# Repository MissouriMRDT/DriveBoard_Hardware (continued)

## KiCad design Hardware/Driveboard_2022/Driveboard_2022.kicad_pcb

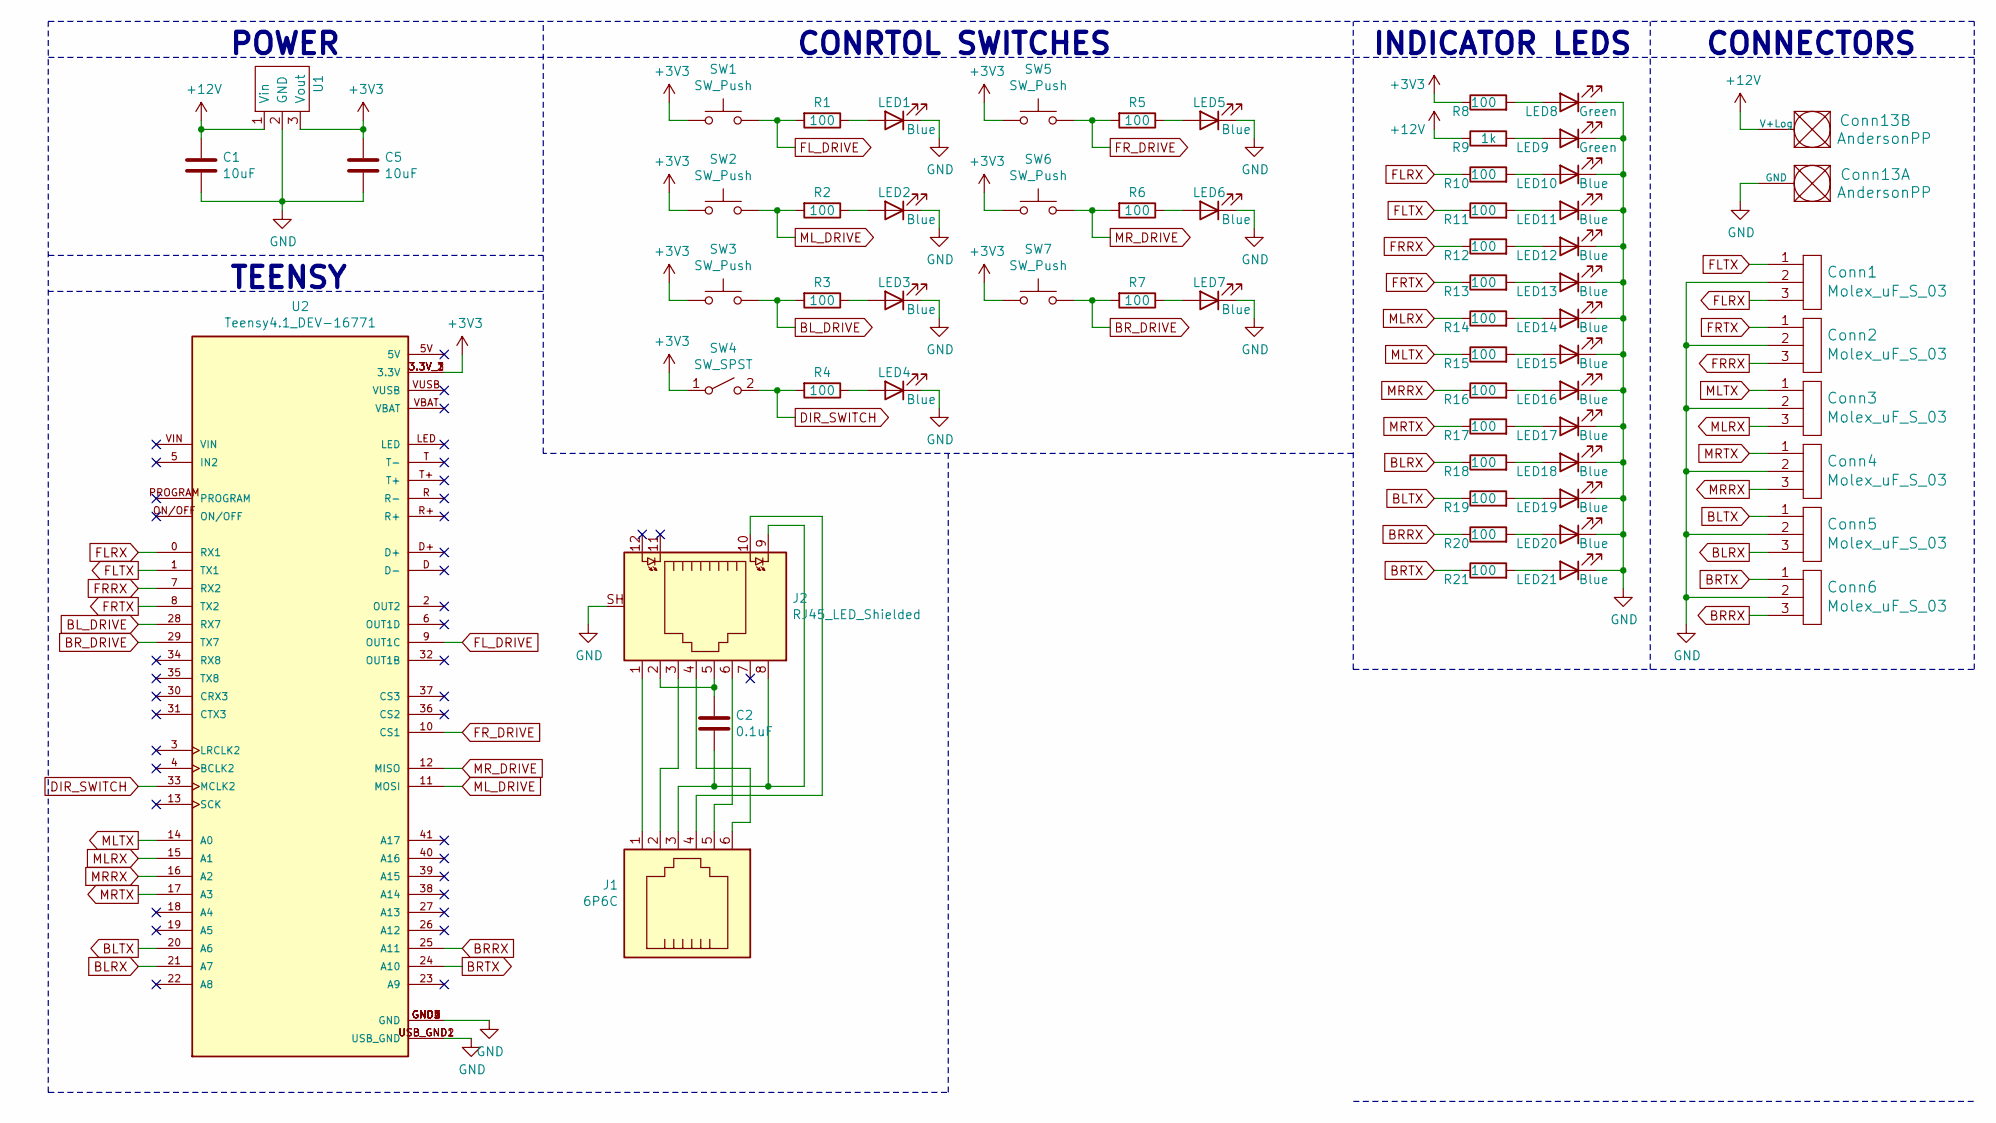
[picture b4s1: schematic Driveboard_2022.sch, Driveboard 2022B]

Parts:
C1, C5: 10uF; C_0603_1608Metric_Pad1.08x0.95mm_HandSolder
C2: 0.1uF; C_0603_1608Metric_Pad1.08x0.95mm_HandSolder
Conn1, Conn2, Conn3, Conn4, Conn5, Conn6: Molex_uF_S_03; MOLEX_uF_S_03_Horizontal
Conn13: AndersonPP; Anderson_2_Horizontal_Side_by_Side
J1: 6P6C; PinHeader_2x03_P2.00mm_Vertical
J2: RJ45_LED_Shielded; RJ45_Teensy
LED1, LED2, LED3, LED4, LED5, LED6, LED7, LED10, LED11, LED12, LED13, LED14, LED15, LED16, LED17, LED18, LED19, LED20, LED21: Blue; LED_0603_1608Metric_Pad1.05x0.95mm_HandSolder
LED8, LED9: Green; LED_0603_1608Metric_Pad1.05x0.95mm_HandSolder
R1, R2, R3, R4, R5, R6, R7, R8, R10, R11, R12, R13, R14, R15, R16, R17, R18, R19, R20, R21: 100; R_0603_1608Metric_Pad0.98x0.95mm_HandSolder
R9: 1k; R_0603_1608Metric_Pad0.98x0.95mm_HandSolder
SW1, SW2, SW3, SW5, SW6, SW7: SW_Push; SW_SPST_TL3305A
SW4: SW_SPST; SW_Slide_1P2T_CK_OS102011MS2Q
U1: TSR1-2433; TSR_1-2433
U2: Teensy4.1_DEV-16771; Teensy_4_1_Vertical; PARTREV 4.1

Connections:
+3V3: C5.1, R8.1, SW1.1, SW2.1, SW3.1, SW4.1 (A), SW5.1, SW6.1, SW7.1, U1.3 (Vout), U2.3.3V_1 (3.3V), U2.3.3V_2 (3.3V), U2.3.3V_3 (3.3V)
+12V: C1.1, Conn13.2 (V+Log), R9.1, U1.1 (Vin)
BLRX: Conn5.3, R18.1, U2.21 (A7)
BLTX: Conn5.1, R19.1, U2.20 (A6)
BL_DRIVE: R3.2, SW3.2, U2.28 (RX7)
BRRX: Conn6.3, R20.1, U2.25 (A11)
BRTX: Conn6.1, R21.1, U2.24 (A10)
BR_DRIVE: R7.2, SW7.2, U2.29 (TX7)
DIR_SWITCH: R4.2, SW4.2 (B), U2.33 (MCLK2)
FLRX: Conn1.3, R10.1, U2.0 (RX1)
FLTX: Conn1.1, R11.1, U2.1 (TX1)
FL_DRIVE: R1.2, SW1.2, U2.9 (OUT1C)
FRRX: Conn2.3, R12.1, U2.7 (RX2)
FRTX: Conn2.1, R13.1, U2.8 (TX2)
FR_DRIVE: R5.2, SW5.2, U2.10 (CS1)
GND: C1.2, C5.2, Conn1.2, Conn2.2, Conn3.2, Conn4.2, Conn5.2, Conn6.2, Conn13.1 (GND), J2.SH, LED1.1 (K), LED2.1 (K), LED3.1 (K), LED4.1 (K), LED5.1 (K), LED6.1 (K), LED7.1 (K), LED8.1 (K), LED9.1 (K), LED10.1 (K), LED11.1 (K), LED12.1 (K), LED13.1 (K), LED14.1 (K), LED15.1 (K), LED16.1 (K), LED17.1 (K), LED18.1 (K), LED19.1 (K), LED20.1 (K), LED21.1 (K), U1.2 (GND), U2.GND1 (GND), U2.GND2 (GND), U2.GND3 (GND), U2.GND4 (GND), U2.GND5 (GND), U2.USB_GND1 (USB_GND), U2.USB_GND2 (USB_GND)
MLRX: Conn3.3, R14.1, U2.15 (A1)
MLTX: Conn3.1, R15.1, U2.14 (A0)
ML_DRIVE: R2.2, SW2.2, U2.11 (MOSI)
MRRX: Conn4.3, R16.1, U2.16 (A2)
MRTX: Conn4.1, R17.1, U2.17 (A3)
MR_DRIVE: R6.2, SW6.2, U2.12 (MISO)
unnamed: C2.1, J2.2, J2.5
unnamed: C2.2, J1.3, J2.8, J2.9
unnamed: J1.1, J2.1
unnamed: J1.2, J2.3
unnamed: J1.4, J2.10
unnamed: J1.5, J2.6
unnamed: J1.6, J2.4
unnamed: LED1.2 (A), R1.1
unnamed: LED2.2 (A), R2.1
unnamed: LED3.2 (A), R3.1
unnamed: LED4.2 (A), R4.1
unnamed: LED5.2 (A), R5.1
unnamed: LED6.2 (A), R6.1
unnamed: LED7.2 (A), R7.1
unnamed: LED8.2 (A), R8.2
unnamed: LED9.2 (A), R9.2
unnamed: LED10.2 (A), R10.2
unnamed: LED11.2 (A), R11.2
unnamed: LED12.2 (A), R12.2
unnamed: LED13.2 (A), R13.2
unnamed: LED14.2 (A), R14.2
unnamed: LED15.2 (A), R15.2
unnamed: LED16.2 (A), R16.2
unnamed: LED17.2 (A), R17.2
unnamed: LED18.2 (A), R18.2
unnamed: LED19.2 (A), R19.2
unnamed: LED20.2 (A), R20.2
unnamed: LED21.2 (A), R21.2

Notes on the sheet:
POWER
INDICATOR LEDS
CONNECTORS
CONRTOL SWITCHES
TEENSY

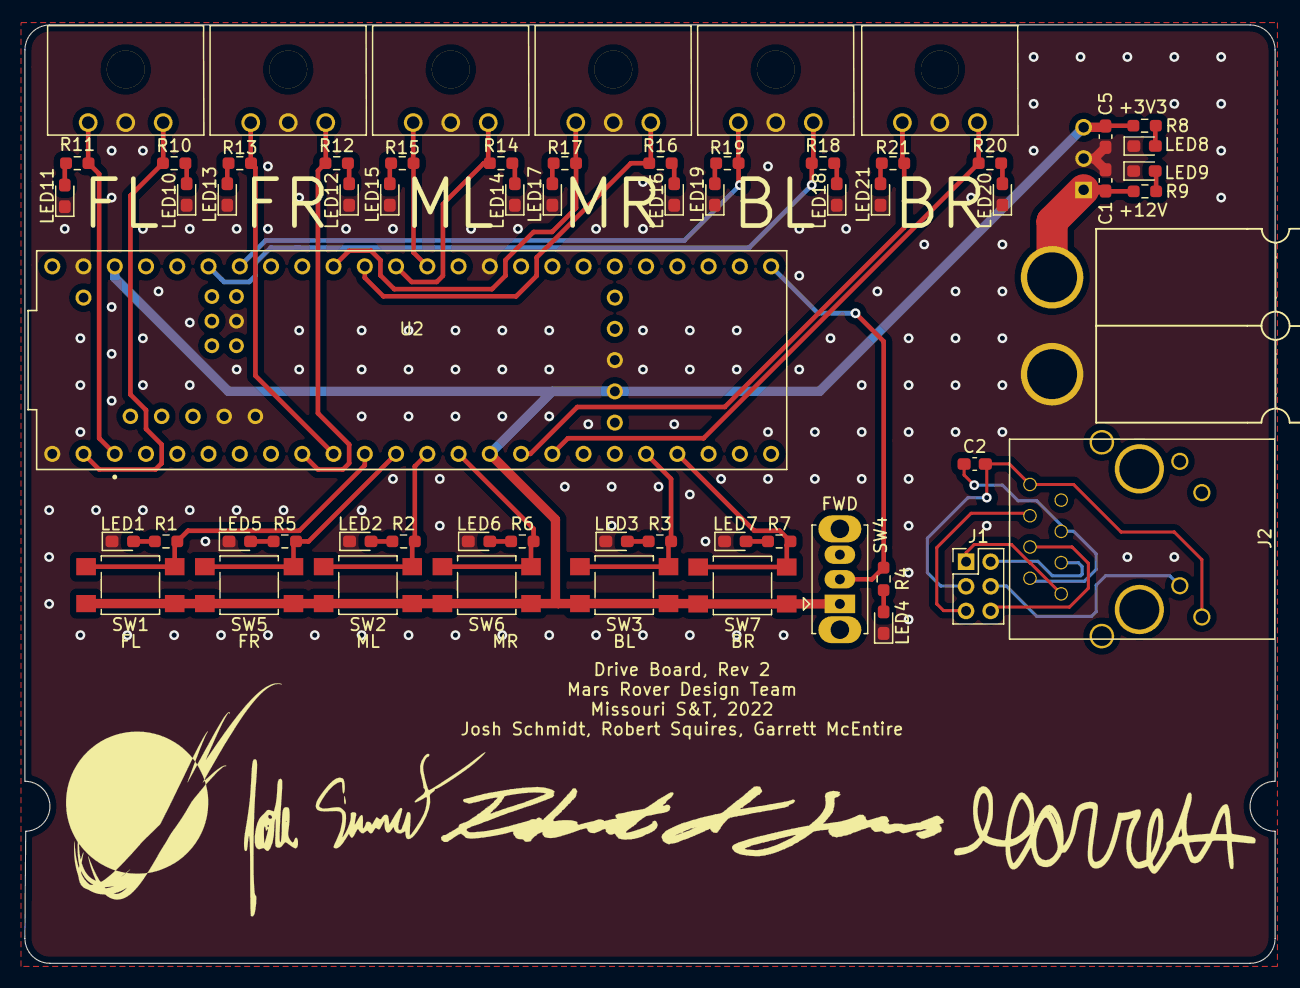
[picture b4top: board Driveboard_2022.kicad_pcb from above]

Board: 2 copper layers, 101.6 x 76.3 mm, 63 parts (1 on the bottom side), 50 nets.

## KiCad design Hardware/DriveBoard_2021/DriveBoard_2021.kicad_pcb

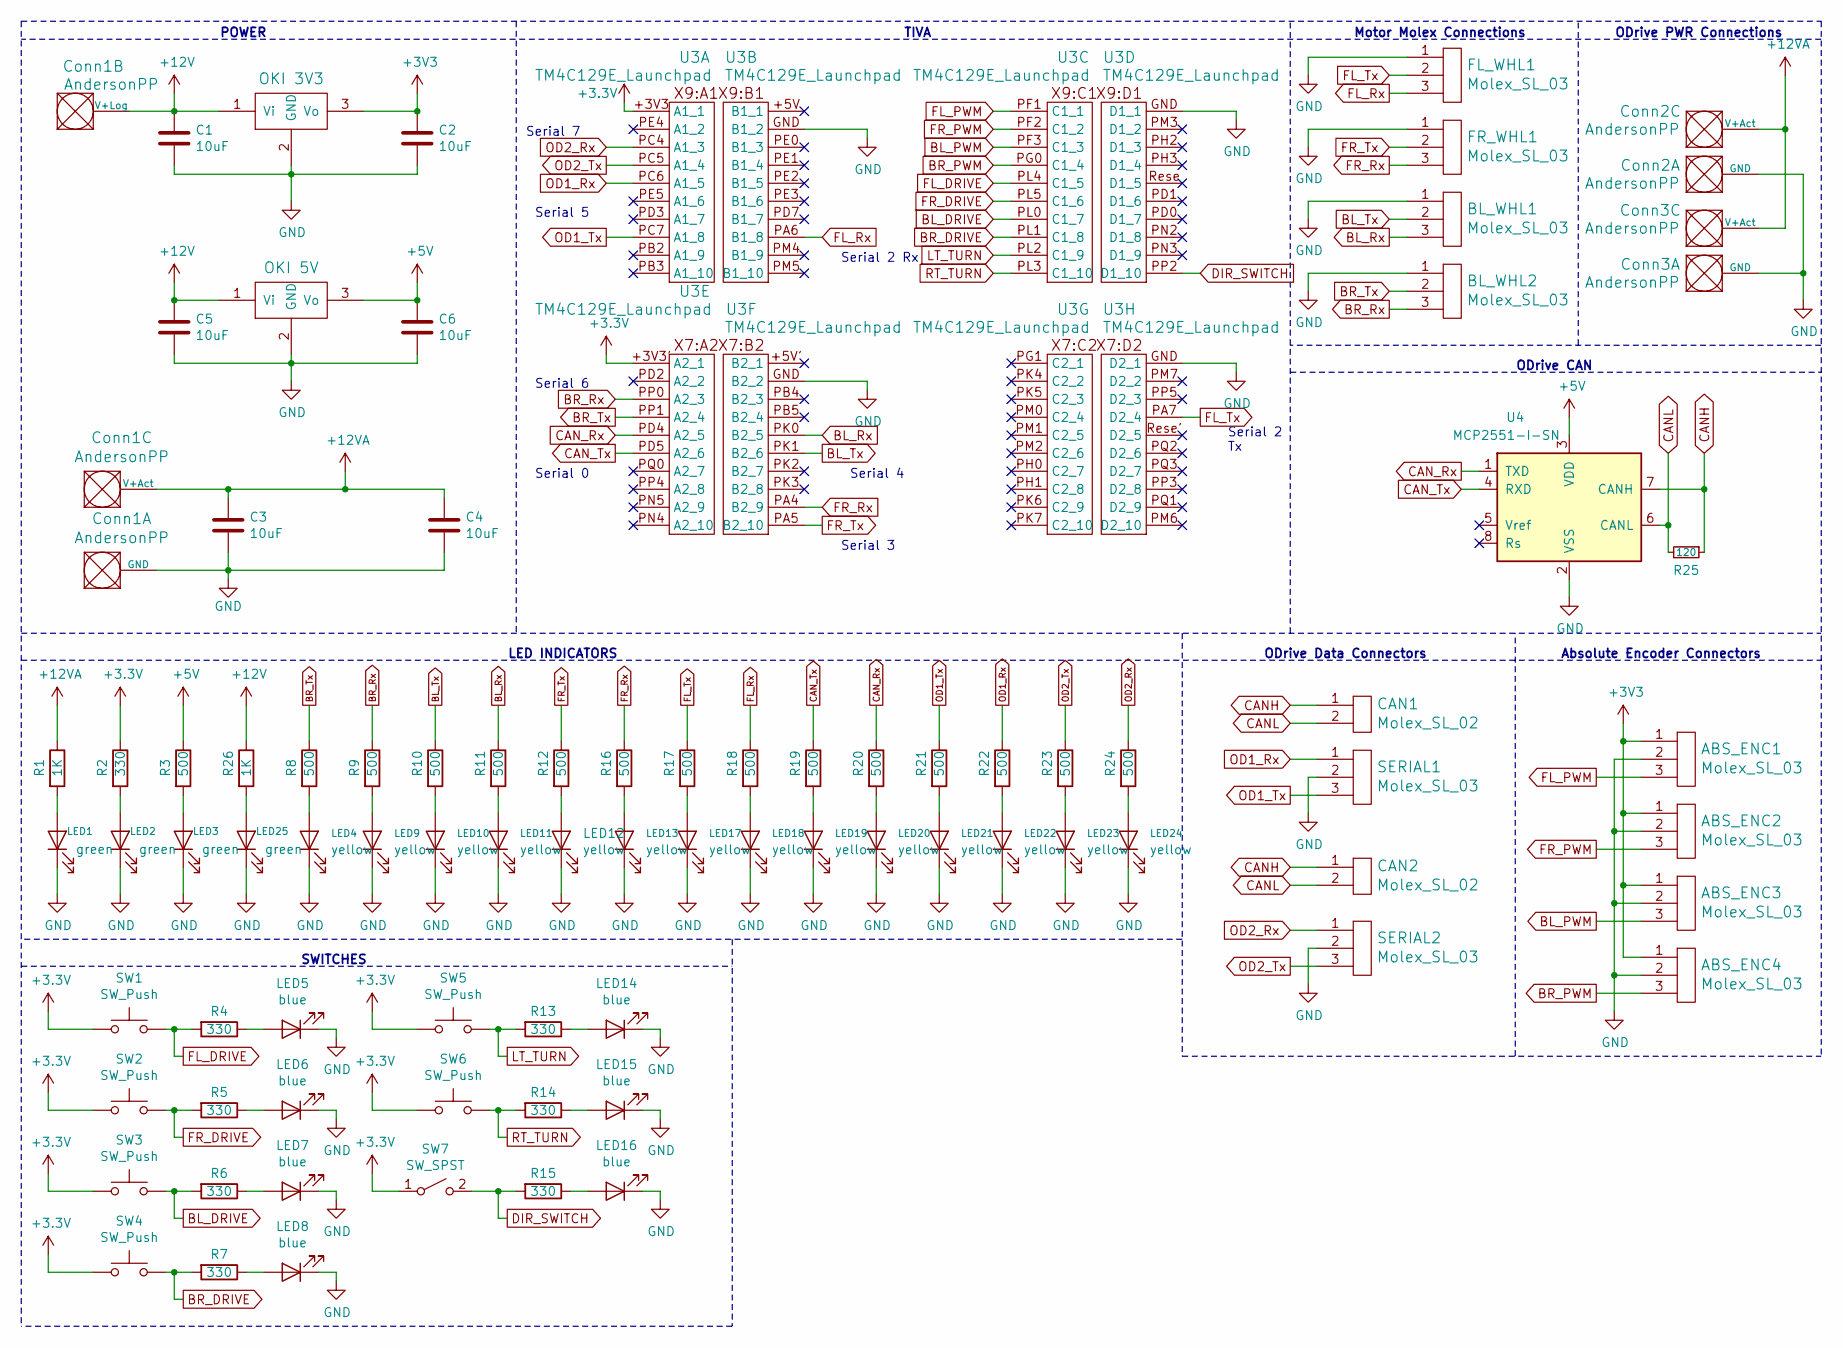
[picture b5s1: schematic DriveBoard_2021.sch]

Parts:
ABS_ENC1, ABS_ENC2, ABS_ENC3, ABS_ENC4: Molex_SL_03; MOLEX_SL_03_Horizontal
BL_WHL1, BL_WHL2: Molex_SL_03; MOLEX_SL_03_Horizontal
C1, C2, C3, C4, C5, C6: 10uF; C_0603_1608Metric_Pad1.05x0.95mm_HandSolder
CAN1, CAN2: Molex_SL_02; MOLEX_SL_02_Horizontal
Conn1: AndersonPP; Anderson_3_Horizontal_Side_by_Side
Conn2, Conn3: AndersonPP; Anderson_2_Horizontal_Side_by_Side
FL_WHL1: Molex_SL_03; MOLEX_SL_03_Horizontal
FR_WHL1: Molex_SL_03; MOLEX_SL_03_Horizontal
LED1, LED2, LED3, LED25: green; LED_0603_1608Metric_Pad1.05x0.95mm_HandSolder
LED4, LED9, LED10, LED11, LED12, LED13, LED17, LED18, LED19, LED20, LED21, LED22, LED23, LED24: yellow; LED_0603_1608Metric_Pad1.05x0.95mm_HandSolder
LED5, LED6, LED7, LED8, LED14, LED15, LED16: blue; LED_0603_1608Metric_Pad1.05x0.95mm_HandSolder
R1, R26: 1K; R_0603_1608Metric_Pad1.05x0.95mm_HandSolder
R2, R4, R5, R6, R7, R13, R14, R15: 330; R_0603_1608Metric_Pad1.05x0.95mm_HandSolder
R3, R8, R9, R10, R11, R12, R16, R17, R18, R19, R20, R21, R22, R23, R24: 500; R_0603_1608Metric_Pad1.05x0.95mm_HandSolder
R25: 120; R_0603_1608Metric_Pad1.05x0.95mm_HandSolder
SERIAL1, SERIAL2: Molex_SL_03; MOLEX_SL_03_Horizontal
SW1, SW2, SW3, SW4, SW5, SW6: SW_Push; SW_SPST_TL3305A
SW7: SW_SPST; SW_CuK_JS202011CQN_DPDT_Straight
U1: OKI 3V3; OKI_Horizontal
U2: OKI 5V; OKI_Horizontal
U3: TM4C129E_Launchpad; TM4C129E_Launchpad_FULL_THT_BOTTOM
U4: MCP2551-I-SN; SOIC-8_3.9x4.9mm_P1.27mm

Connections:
+5V: C6.1, R3.1, U2.3 (Vo), U4.3 (VDD)
+12V: C1.1, C5.1, Conn1.2 (V+Log), R26.1, U1.1 (Vi), U2.1 (Vi)
+12VA: C3.1, C4.1, Conn1.3 (V+Act), Conn2.2 (V+Log), Conn3.2 (V+Log), R1.1
BL_DRIVE: R6.2, SW3.2, U3.PL0 (C1_7)
BL_PWM: ABS_ENC3.3, U3.PF3 (C1_3)
BL_Rx: BL_WHL1.3, R11.1, U3.PK0 (B2_5)
BL_Tx: BL_WHL1.2, R10.1, U3.PK1 (B2_6)
BR_DRIVE: R7.2, SW4.2, U3.PL1 (C1_8)
BR_PWM: ABS_ENC4.3, U3.PG0 (C1_4)
BR_Rx: BL_WHL2.3, R9.1, U3.PP0 (A2_3)
BR_Tx: BL_WHL2.2, R8.1, U3.PP1 (A2_4)
CANH: CAN1.1, CAN2.1, R25.1, U4.7 (CANH)
CANL: CAN1.2, CAN2.2, R25.2, U4.6 (CANL)
CAN_Rx: R20.1, U3.PD4 (A2_5), U4.1 (TXD)
CAN_Tx: R19.1, U3.PD5 (A2_6), U4.4 (RXD)
DIR_SWITCH: R15.2, SW7.2 (B), U3.PP2 (D1_10)
FL_DRIVE: R4.2, SW1.2, U3.PL4 (C1_5)
FL_PWM: ABS_ENC1.3, U3.PF1 (C1_1)
FL_Rx: FL_WHL1.3, R18.1, U3.PA6 (B1_8)
FL_Tx: FL_WHL1.2, R17.1, U3.PA7 (D2_4)
FR_DRIVE: R5.2, SW2.2, U3.PL5 (C1_6)
FR_PWM: ABS_ENC2.3, U3.PF2 (C1_2)
FR_Rx: FR_WHL1.3, R16.1, U3.PA4 (B2_9)
FR_Tx: FR_WHL1.2, R12.1, U3.PA5 (B2_10)
GND: ABS_ENC1.2, ABS_ENC2.2, ABS_ENC3.2, ABS_ENC4.2, BL_WHL1.1, BL_WHL2.1, C1.2, C2.2, C3.2, C4.2, C5.2, C6.2, Conn1.1 (GND), Conn2.1 (GND), Conn3.1 (GND), FL_WHL1.1, FR_WHL1.1, LED1.1 (K), LED2.1 (K), LED3.1 (K), LED4.1 (K), LED5.1 (K), LED6.1 (K), LED7.1 (K), LED8.1 (K), LED9.1 (K), LED10.1 (K), LED11.1 (K), LED12.1 (K), LED13.1 (K), LED14.1 (K), LED15.1 (K), LED16.1 (K), LED17.1 (K), LED18.1 (K), LED19.1 (K), LED20.1 (K), LED21.1 (K), LED22.1 (K), LED23.1 (K), LED24.1 (K), LED25.1 (K), SERIAL1.2, SERIAL2.2, U1.2 (GND), U2.2 (GND), U3.GND (B1_2), U4.2 (VSS)
LT_TURN: R13.2, SW5.2, U3.PL2 (C1_9)
unnamed: LED1.2 (A), R1.2
unnamed: LED2.2 (A), R2.2
unnamed: LED3.2 (A), R3.2
unnamed: LED4.2 (A), R8.2
unnamed: LED5.2 (A), R4.1
unnamed: LED6.2 (A), R5.1
unnamed: LED7.2 (A), R6.1
unnamed: LED8.2 (A), R7.1
unnamed: LED9.2 (A), R9.2
unnamed: LED10.2 (A), R10.2
unnamed: LED11.2 (A), R11.2
unnamed: LED12.2 (A), R12.2
unnamed: LED13.2 (A), R16.2
unnamed: LED14.2 (A), R13.1
unnamed: LED15.2 (A), R14.1
unnamed: LED16.2 (A), R15.1
unnamed: LED17.2 (A), R17.2
unnamed: LED18.2 (A), R18.2
unnamed: LED19.2 (A), R19.2
unnamed: LED20.2 (A), R20.2
unnamed: LED21.2 (A), R21.2
unnamed: LED22.2 (A), R22.2
unnamed: LED23.2 (A), R23.2
unnamed: LED24.2 (A), R24.2
unnamed: LED25.2 (A), R26.2
OD1_Rx: R22.1, SERIAL1.1, U3.PC6 (A1_5)
OD1_Tx: R21.1, SERIAL1.3, U3.PC7 (A1_8)
OD2_Rx: R24.1, SERIAL2.1, U3.PC4 (A1_3)
OD2_Tx: R23.1, SERIAL2.3, U3.PC5 (A1_4)
RT_TURN: R14.2, SW6.2, U3.PL3 (C1_10)

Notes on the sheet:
POWER
SWITCHES
LED INDICATORS
TIVA
Serial 4
Serial 3
Serial 6
Serial 2 Rx
Serial 2 Tx
Motor Molex Connections
ODrive PWR Connections
Serial 0
ODrive CAN
Serial 5
Serial 7
Absolute Encoder Connectors
ODrive Data Connectors

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
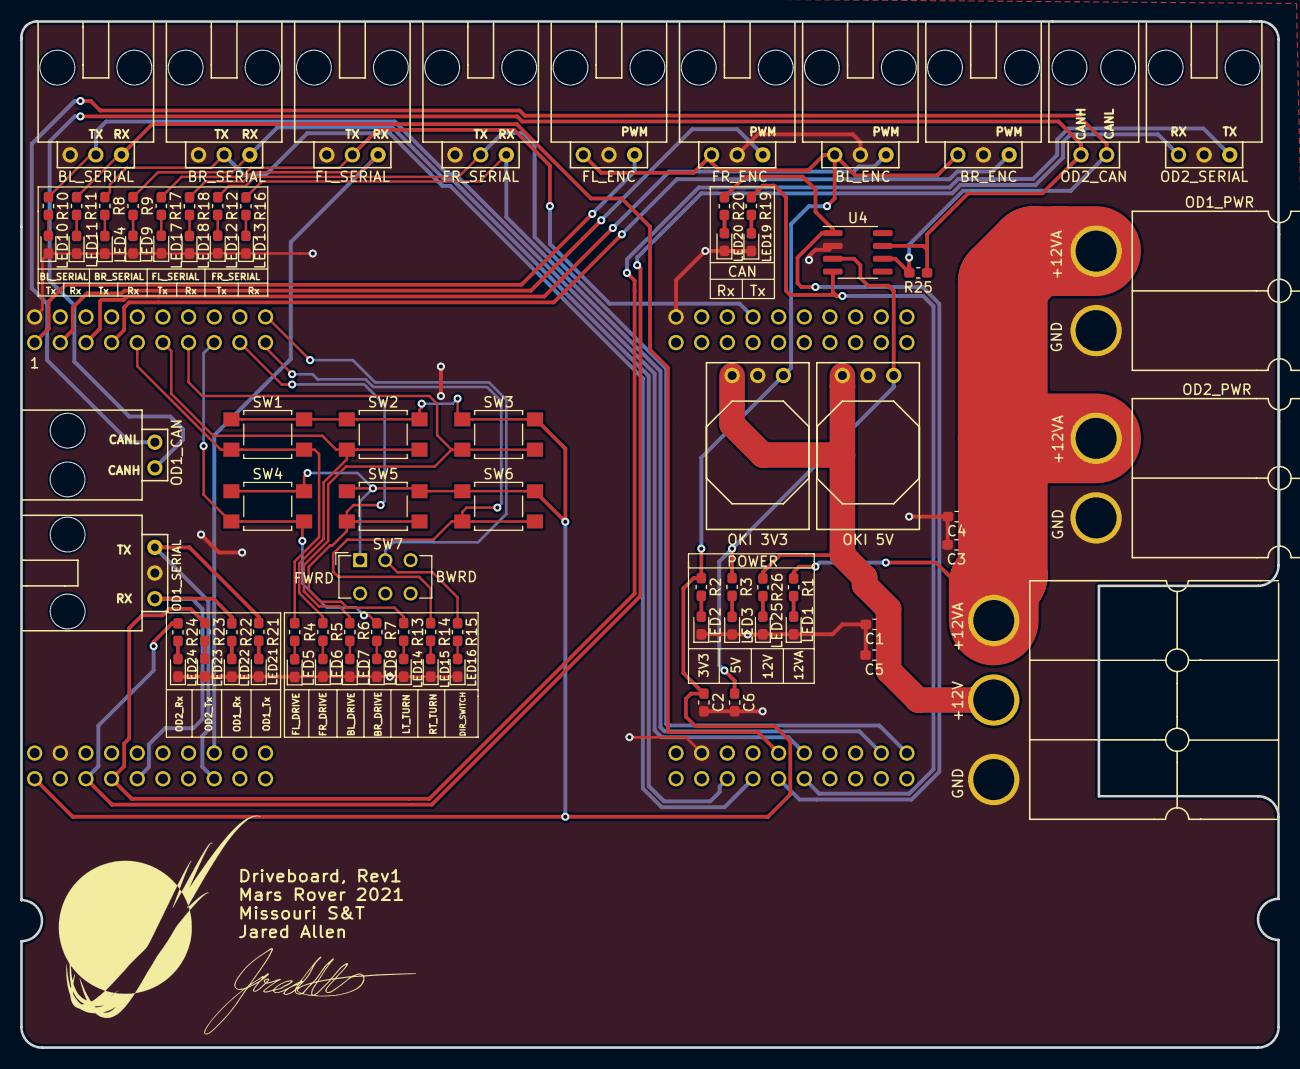
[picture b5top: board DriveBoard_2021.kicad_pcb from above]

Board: 2 copper layers, 124.5 x 101.6 mm, 83 parts (0 on the bottom side), 57 nets.

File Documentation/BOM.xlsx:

Id | Designator | Package | Quantity | Designation | Supplier and ref
1 | R11,R3,R8,R9,R10,R12,R16,R17,R18,R19,R20,R21,R22,R23,R24 | R_0603_1608Metric_Pad1.05x0.95mm_HandSolder | 15 | 500
2 | U3 | TM4C129E_Launchpad_FULL_THT_BOTTOM | 1 | TM4C129E_Launchpad
3 | G*** | 0_MRDT_Logo_20mm | 1 | LOGO
4 | G*** | z_sig_Jared_Allen | 1 | LOGO
5 | Conn1 | Anderson_3_Horizontal_Side_by_Side | 1 | AndersonPP
6 | FR_WHL1,FL_WHL1,BL_WHL2,BL_WHL1,ABS_ENC4,ABS_ENC3,ABS_ENC2,ABS_ENC1,SERIAL1,SER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 | MOLEX_SL_03_Horizontal | 10 | Molex_SL_03
7 | Conn3,Conn2 | Anderson_2_Horizontal_Side_by_Side | 2 | AndersonPP
8 | CAN2,CAN1 | MOLEX_SL_02_Horizontal | 2 | Molex_SL_02
9 | C1,C2,C3,C4,C5,C6 | C_0603_1608Metric_Pad1.05x0.95mm_HandSolder | 6 | 10uF
10 | LED1,LED2,LED3,LED25 | LED_0603_1608Metric_Pad1.05x0.95mm_HandSolder | 4 | green
11 | LED4,LED9,LED10,LED11,LED12,LED13,LED17,LED18,LED19,LED20,LED21,LED22,LED23,LED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 | LED_0603_1608Metric_Pad1.05x0.95mm_HandSolder | 14 | pink
12 | LED5,LED6,LED7,LED8,LED14,LED15,LED16 | LED_0603_1608Metric_Pad1.05x0.95mm_HandSolder | 7 | yellow
13 | R1,R26 | R_0603_1608Metric_Pad1.05x0.95mm_HandSolder | 2 | 1K
14 | R2,R4,R5,R6,R7,R13,R14,R15 | R_0603_1608Metric_Pad1.05x0.95mm_HandSolder | 8 | 330
15 | R25 | R_0603_1608Metric_Pad1.05x0.95mm_HandSolder | 1 | 120
16 | FL_DRIVE,FR_DRIVE,BL_DRIVE,BR_DRIVE,LT_TURN,RT_TURN | SW_SPST_TL3305A | 6 | SW_Push
17 | DIR_SWITCH | SW_CuK_JS202011CQN_DPDT_Straight | 1 | SW_SPST
18 | U1 | OKI_Horizontal | 1 | OKI 3V3
19 | U2 | OKI_Horizontal | 1 | OKI 5V
20 | CAN | SOIC-8_3.9x4.9mm_P1.27mm | 1 | MCP2551-I-SN

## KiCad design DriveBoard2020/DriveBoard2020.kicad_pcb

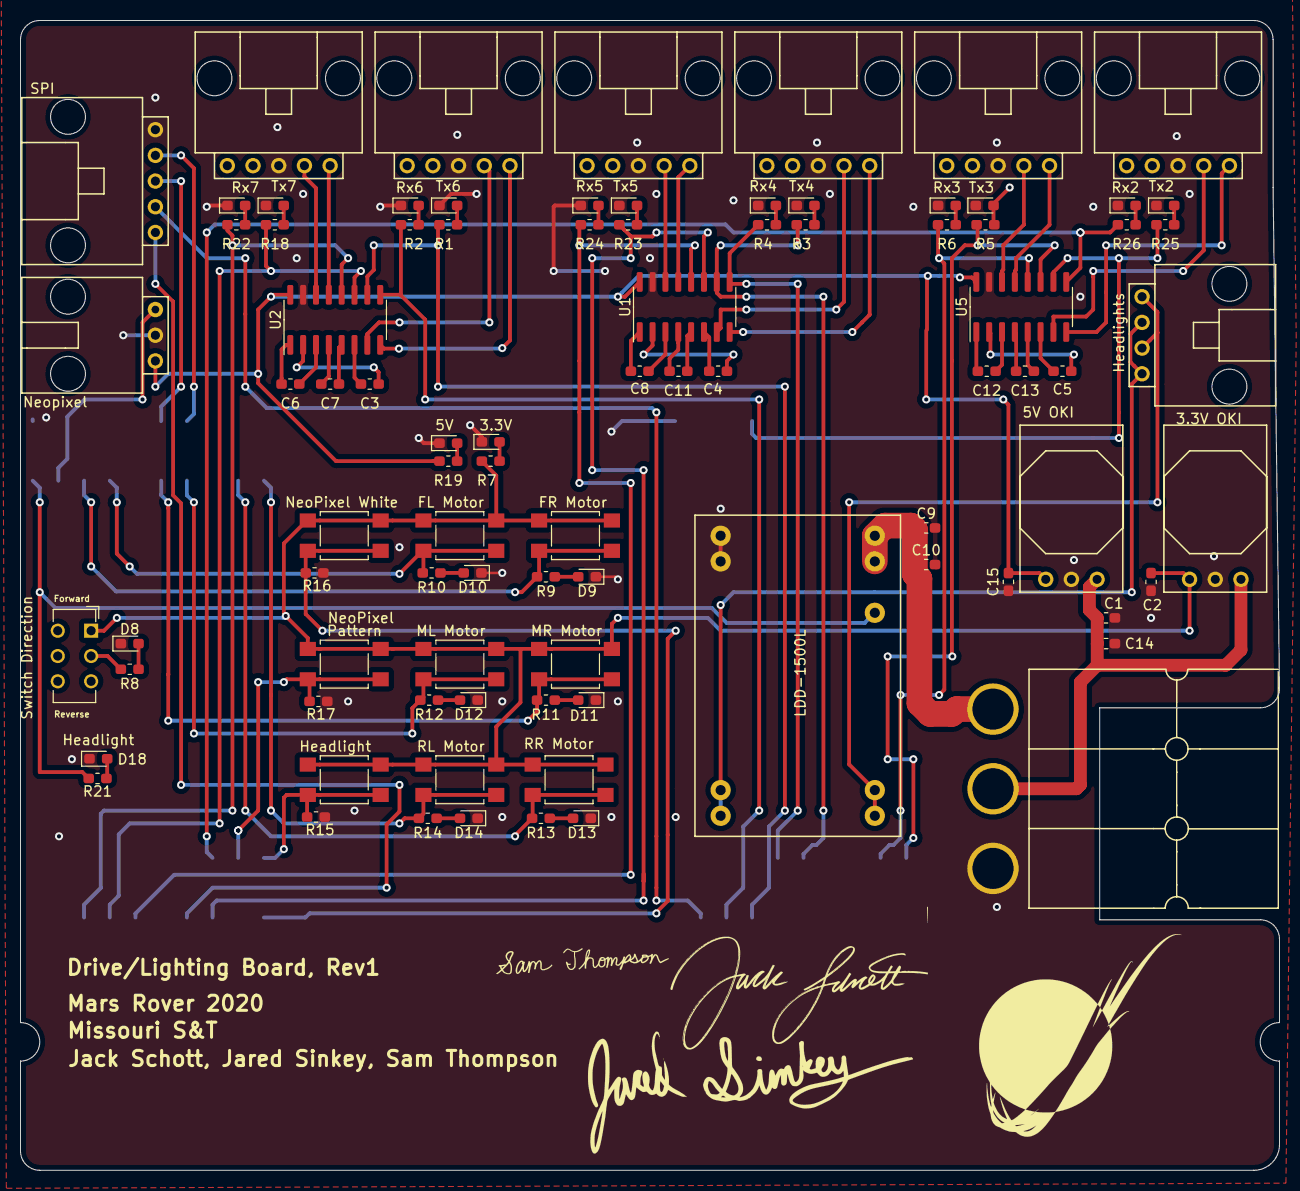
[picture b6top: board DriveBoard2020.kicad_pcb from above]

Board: 2 copper layers, 124.5 x 113.7 mm, 89 parts (0 on the bottom side), 87 nets.

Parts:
3.3V, 5V: LED; LED_0603_1608Metric_Pad1.05x0.95mm_HandSolder
C1, C2, C9, C10, C14, C15: 10uF; C_0603_1608Metric_Pad1.05x0.95mm_HandSolder
C3, C4, C5: 1uF; C_0603_1608Metric_Pad1.05x0.95mm_HandSolder
C6, C7, C8, C11, C12, C13: .1uF; C_0603_1608Metric_Pad1.05x0.95mm_HandSolder
Conn1: AndersonPP; Anderson_3_Horizontal_Side_by_Side
Conn2, Conn3, Conn4, Conn5, Conn6, Conn7, Conn12: Molex_SL_05; MOLEX_SL_05_Horizontal
Conn9: Molex_SL_03; MOLEX_SL_03_Horizontal
Conn10: Molex_SL_04; MOLEX_SL_04_Horizontal
D8, D9, D10, D11, D12, D13, D14: LED; LED_0603_1608Metric_Pad1.05x0.95mm_HandSolder
FL Motor: SW_Push; SW_SPST_TL3305A
FR Motor: SW_Push; SW_SPST_TL3305A
Headlight: SW_Push; SW_SPST_TL3305A
Headlight#2: LED; LED_0603_1608Metric_Pad1.05x0.95mm_HandSolder
ML Motor: SW_Push; SW_SPST_TL3305A
MR Motor: SW_Push; SW_SPST_TL3305A
NeoPixel White: SW_Push; SW_SPST_TL3305A
Pattern: SW_Push; SW_SPST_TL3305A
R1, R2, R3, R4, R5, R6, R18, R19, R21, R22, R23, R24, R25, R26: 500; R_0603_1608Metric_Pad1.05x0.95mm_HandSolder
R7, R8, R9, R10, R11, R12, R13, R14: 330; R_0603_1608Metric_Pad1.05x0.95mm_HandSolder
R15, R16, R17: 10k; R_0603_1608Metric_Pad1.05x0.95mm_HandSolder
RL Motor: SW_Push; SW_SPST_TL3305A
RR Motor: SW_Push; SW_SPST_TL3305A
Rx2, Rx3, Rx4, Rx5, Rx6, Rx7: LED; LED_0603_1608Metric_Pad1.05x0.95mm_HandSolder
Switch Direction: SW_SPST; SW_CuK_JS202011CQN_DPDT_Straight
Tx2, Tx3, Tx4, Tx5, Tx6, Tx7: LED; LED_0603_1608Metric_Pad1.05x0.95mm_HandSolder
U1, U2, U5: MAX_3232; SOIC-16_3.9x9.9mm_P1.27mm
U3: 3.3V OKI; OKI_Horizontal
U4: TM4C129E_Launchpad; TM4C129E_Launchpad_FULL_SMD_BOTTOM
U6: 5V OKI; OKI_Horizontal
U8: LDD-1500L; LDD-1500L_LED_DRIVER

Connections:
+3V3: C2.1, FL Motor.1, FR Motor.1, Headlight.1, ML Motor.1, MR Motor.1, NeoPixel White.1, Pattern.1, R7.1, RL Motor.1, RR Motor.1, Switch Direction.1, U3.3
+5V: C15.1, Conn9.1, R19.1, U1.16, U2.16, U5.16, U6.3
+12V: C1.1, C14.1, Conn1.2, U3.1, U6.1
+12VA: C9.1, C10.1, Conn1.3, U8.23, U8.24
CLK2: Conn12.1, U4.PD3
CS2: Conn12.2, U4.PD2
Dout_NeoPixel: Conn9.3, U4.PF2
FL_In: Conn2.5, U2.13
FL_Motor: FL Motor.2, R10.2, U4.PG0
FL_Out: Conn2.4, U2.14
FR_In: Conn5.5, U2.8
FR_Motor: FR Motor.2, R9.2, U4.PF3
FR_Out: Conn5.4, U2.7
GND: 3.3V.1, 5V.1, C1.2, C2.2, C9.2, C10.2, C14.2, C15.2, Conn1.1, Conn2.3, Conn3.3, Conn4.3, Conn5.3, Conn6.3, Conn7.3, Conn9.2, Conn12.5, D8.1, D9.1, D10.1, D11.1, D12.1, D13.1, D14.1, Headlight#2.1, R15.1, R16.1, R17.1, Rx2.1, Rx3.1, Rx4.1, Rx5.1, Rx6.1, Rx7.1, Tx2.1, Tx3.1, Tx4.1, Tx5.1, Tx6.1, Tx7.1, U1.15, U2.15, U3.2, U4.GND, U5.15, U6.2, U8.1, U8.2
Headlight_OnOff_PWM: R21.1, U4.PF1, U8.21
Headlight_Power: Headlight.2, R15.2, U4.PM5
MISO2: Conn12.4, U4.PD0
ML_In: Conn3.5, U1.13
ML_Motor: ML Motor.2, R12.2, U4.PL0
ML_Out: Conn3.4, U1.14
MOSI2: Conn12.3, U4.PD1
MR_In: Conn6.5, U1.8
MR_Motor: MR Motor.2, R11.2, U4.PL5
MR_Out: Conn6.4, U1.7
NeoPixel_Pattern: Pattern.2, R17.2, U4.PM4
NeoPixel_White: NeoPixel White.2, R16.2, U4.PB3
unnamed: C3.1, U2.2
unnamed: C3.2, U2.6
unnamed: C4.1, U1.2
unnamed: C4.2, U1.6
unnamed: C5.1, U5.2
unnamed: C5.2, U5.6
unnamed: C6.1, U2.1
unnamed: C6.2, U2.3
unnamed: C7.1, U2.4
unnamed: C7.2, U2.5
unnamed: C8.1, U1.1
unnamed: C8.2, U1.3
unnamed: C11.1, U1.4
unnamed: C11.2, U1.5
unnamed: C12.1, U5.1
unnamed: C12.2, U5.3
unnamed: C13.1, U5.4
unnamed: C13.2, U5.5
unnamed: Conn10.1, Conn10.3, U8.13, U8.14
unnamed: Conn10.2, Conn10.4, U8.11, U8.12
unnamed: R1.2, Tx6.2
unnamed: R2.2, Rx6.2
unnamed: R3.2, Tx4.2
unnamed: R4.2, Rx4.2
unnamed: R5.2, Tx3.2
unnamed: R6.2, Rx3.2
unnamed: 3.3V.2, R7.2
unnamed: D8.2, R8.1
unnamed: D9.2, R9.1
unnamed: D10.2, R10.1
unnamed: D11.2, R11.1
unnamed: D12.2, R12.1
unnamed: D13.2, R13.1
unnamed: D14.2, R14.1
unnamed: R18.2, Tx7.2
unnamed: 5V.2, R19.2
unnamed: Headlight#2.2, R21.2
unnamed: R22.2, Rx7.2
unnamed: R23.2, Tx5.2
unnamed: R24.2, Rx5.2
unnamed: R25.2, Tx2.2
unnamed: R26.2, Rx2.2
RL_In: Conn4.5, U5.13
RL_Motor: R14.2, RL Motor.2, U4.PL3
RL_Out: Conn4.4, U5.14
RR_In: Conn7.5, U5.8
RR_Motor: R13.2, RR Motor.2, U4.PL2
RR_Out: Conn7.4, U5.7
Rx2: R26.1, U4.PA6, U5.9
Rx3: R6.1, U4.PA4, U5.12
Rx4: R4.1, U1.9, U4.PK0
Rx5: R24.1, U1.12, U4.PC6
Rx6: R2.1, U2.9, U4.PP0
Rx7: R22.1, U2.12, U4.PC4
Tx2: R25.1, U4.PA7, U5.10
Tx3: R5.1, U4.PA5, U5.11
Tx4: R3.1, U1.10, U4.PK1
Tx5: R23.1, U1.11, U4.PC7
Tx6: R1.1, U2.10, U4.PP1
Tx7: R18.1, U2.11, U4.PC5
switch_direction: R8.2, Switch Direction.2

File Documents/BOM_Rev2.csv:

Id,Designator,Package,,Designation,Item Name,Part Number,,Vendor,Quantity,Cost Per Item,,Cost,URL,Comments
1,U4,TM4C129E_Launchpad_FULL_THT_BOTTOM,,TM4C129E_Launchpad,LAUNCHPAD TM4C129E EVAL BRD,296-44249-ND,,digikey,1,25.95,,25.95,https://www.digikey.com/products/en?keywords=tm4c129e%20launchpad,
2,"C1,C2,C9,C10,C14,C15",C_0603_1608Metric_Pad1.05x0.95mm_HandSolder,,10uF,CAP CER 10UF 6.3V X5R 0603,1276-3105-6-ND,,digikey,6,0.29,,1.74,https://www.digikey.com/product-detail/en/samsung-electro-me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,
3,"C3,C4,C5",C_0603_1608Metric_Pad1.05x0.95mm_HandSolder,,1uF,CAP CER 1UF 616V X7R 0603,1276-6524-1-ND,,digikey,6,0.1,,0.6,https://www.digikey.com/products/en?keywords=1276-6524-1-ND,
4,"C6,C7,C8,C11,C12,C13",C_0603_1608Metric_Pad1.05x0.95mm_HandSolder,,.1uF,CAP CER 0.1UF 16V X7R 0603,1276-1005-1-ND,,digikey,6,0.1,,0.6,https://www.digikey.com/products/en?keywords=1276-1005-1-ND,
5,"D8,D9,D10,D11,D12,D13,D14",LED_0603_1608Metric_Pad1.05x0.95mm_HandSolder,,Orange 0603,LED ORANGE CLEAR SMD,160-1445-1-ND,,digikey,7,0.26,,1.82,https://www.digikey.com/product-detail/en/lite-on-inc/LTST-C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,
6,"Tx2,Rx2,Tx3,Rx3,Tx4,Rx4,Tx5,Rx5,Tx6,Rx6,Tx7,Rx7,",LED_0603_1608Metric_Pad1.05x0.95mm_HandSolder,,Pink 0603,SMD LED - 0603 PINK,n/a,,aliexpress,12,0.64,,7.68,https://www.aliexpress.com/item/32723711697.html?scm=1007.23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,
7,3.3V,LED_0603_1608Metric_Pad1.05x0.95mm_HandSolder,,Green 0603,LED GREEN CLEAR SMD,160-1446-1-ND,,digikey,1,0.28,,0.28,https://www.digikey.com/product-detail/en/lite-on-inc/LTST-C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,
8,5V,LED_0603_1608Metric_Pad1.05x0.95mm_HandSolder,,Yellow 0603,LED YELLOW CLEAR SMD,160-1448-1-ND,,digikey,1,0.28,,0.28,https://www.digikey.com/product-detail/en/lite-on-inc/LTST-C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,
9,"R1,R2,R3,R4,R5,R6,R16,R17,R19,R18,R22,R23,R24,R25,R26",R_0603_1608Metric_Pad1.05x0.95mm_HandSolder,,500,RES SMD 510 OHM 5% 1/4W 0603,RHM510DCT-ND,,digikey,15,0.1,,1.5,https://www.digikey.com/products/en?keywords=RHM510DCT-ND,
10,"R7,R8,R9,R11,R13,R15,R10,R12,R14",R_0603_1608Metric_Pad1.05x0.95mm_HandSolder,,330,RES SMD 330 OHM 5% 1/4W 0603,RHM330DCT-ND,,digikey,9,0.1,,0.9,https://www.digikey.com/product-detail/en/rohm-semiconductor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,
11,"U3,U6",OKI_Horizontal,,OKI,DC DC CONVERTER 3.3V 5W,811-3014-ND,,digikey,2,4.3,,8.6,https://www.digikey.com/products/en?keywords=811-3014-ND,
12,Change Direction,SW_CuK_OS102011MA1QN1_SPDT_Angled,,SW_SPST,SWITCH SLIDE SPDT 100MA 12V,CKN9559-ND,,digikey,1,0.38,,0.38,https://www.digikey.com/products/en?keywords=CKN9559-ND,
13,"Middle Right,Rear Right,Headlights,Neopixel White,Neopixel,Front Left,Middle Left,Rear Left,Front Right",SW_SPST_TL3305A,,SW_Push,SWITCH TACTILE SPST-NO 50MA 12V,EG5350CT-ND,,digikey,9,0.2,,1.8,https://www.digikey.com/products/en?keywords=EG5350CT-ND,
14,"Conn2,Conn3,Conn4,Conn5,Conn6,Conn7,Conn12",MOLEX_SL_05_Vertical,,Molex_SL_05,CONN HEADER R/A 5POS 2.54MM,WM4903-ND,,digikey,7,1.23,,8.61,https://www.digikey.com/products/en?keywords=WM4903-ND,
15,"U1,U2,U5",SOIC-16_3.9x9.9mm_P1.27mm,,MAX_3232,IC TRANSCEIVER FULL 2/2 16SOIC,296-13094-1-ND,,digikey,3,1.89,,5.67,https://www.digikey.com/product-detail/en/texas-instruments/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,
16,"Conn1,Conn8",Anderson_3_Horizontal_Side_by_Side,,AndersonPP,PCB Horizontal Bottom Contact,1336G1,,powerwerx,2,0.55,,1.1,https://powerwerx.com/anderson-printed-circuit-board-pcb-contacts,
16,"Conn1,Conn8",Anderson_3_Horizontal_Side_by_Side,,AndersonPP,Red Housing,1327FP,,powerwerx,1,0.39,,0.39,https://powerwerx.com/anderson-power-fingerproof-pp15-45-housings,
16,"Conn1,Conn8",Anderson_3_Horizontal_Side_by_Side,,AndersonPP,Black Housing,1327G6FP,,powerwerx,1,0.39,,0.39,https://powerwerx.com/anderson-power-fingerproof-pp15-45-housings,
17,"Conn9,Conn11",MOLEX_SL_02_Horizontal,,Molex_SL_02,CONN HEADER R/A 2POS 2.54MM,WM4900-ND,,digikey,2,0.74,,1.48,https://www.digikey.com/products/en?keywords=WM4900-ND,
18,"R15,R16,R17",R_0603_1608Metric_Pad1.05x0.95mm_HandSolder,,10K, RES SMD 10K OHM 1% 1/4W 0603 ,ESR03EZPF1002,,digikey,3,0.13,,0.39,https://www.digikey.com/products/en?keywords=160-1446-1-ND,
19,U8,LDD-1500L_LED_DRIVER,,LDD-1500L,LED DRIVER CC BUCK 2-30V 1.5A,1866-3101-ND,,digikey,1,5.81,,5.81,https://www.digikey.com/products/en?keywords=160-1445-1-ND,
20,Conn10,MOLEX_SL_04_Horizontal,,Molex_SL_04,CONN HEADER R/A 4POS 2.54MM,WM4902-ND,,digikey,1,1.05,,1.05,https://www.digikey.com/products/en?keywords=WM4902-ND,

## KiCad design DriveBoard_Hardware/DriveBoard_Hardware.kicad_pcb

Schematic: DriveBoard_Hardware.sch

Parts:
C1, C2, C3: 10u; C_0603_1608Metric_Pad1.05x0.95mm_HandSolder
C7, C8: 10uF; C_0603_1608Metric_Pad1.05x0.95mm_HandSolder
Conn1: AndersonPP; Anderson_2_Horizontal_Side_by_Side
Conn2, Conn3, Conn4: Molex_SL_05; MOLEX_SL_05_Horizontal
Conn5, Conn6, Conn7: Molex_SL_03; MOLEX_SL_03_Horizontal
D1, D2, D3, D4, D5, D6, D7, D8, D9, D10, D11, D12, D13, D14, D15, D16, D17: LED; LED_0603_1608Metric_Pad1.05x0.95mm_HandSolder
R1, R2, R3, R4, R5, R6, R7, R15, R16, R17: 500; LED_0603_1608Metric_Pad1.05x0.95mm_HandSolder
R8, R9, R10, R11, R12, R13, R14: 500; R_0603_1608Metric_Pad1.05x0.95mm_HandSolder
SW1, SW2, SW3, SW4, SW5, SW6: SW_Push; SW_SPST_TL3305A
SW7: SW_SPDT; SW_CuK_OS102011MA1QN1_SPDT_Angled
U1, U2, U5: MAX3077E; SOIC-8_3.9x4.9mm_P1.27mm
U3: OKI; OKI_Horizontal
U4: TM4C129E_Launchpad; TM4C129E_Launchpad_X7_SMD_BOTTOM

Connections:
+3V3: C1.1, C2.1, C3.1, C8.1, R1.2, SW1.1, SW2.1, SW3.1, SW4.1, SW5.1, SW6.1, SW7.2, U1.1, U2.1, U3.3 (Vo), U4.+3V3', U5.1
/+12V: C7.1, Conn1.2, U3.1 (Vi)
A1: Conn2.1, U1.8; also elsewhere on the board
A2: Conn3.1, U2.8; also elsewhere on the board
A3: Conn4.1, U5.8; also elsewhere on the board
B1: Conn2.2, U1.7; also elsewhere on the board
B2: Conn3.2, U2.7; also elsewhere on the board
B3: Conn4.2, U5.7; also elsewhere on the board
DIRECTION_SW: R14.2, SW7.3, U4.PD2
GND: C1.2, C2.2, C3.2, C7.2, C8.2, Conn1.1, Conn2.3, Conn3.3, Conn4.3, Conn5.2, Conn6.2, Conn7.2, D1.1 (K), D2.1 (K), D3.1 (K), D4.1 (K), D5.1 (K), D6.1 (K), D7.1 (K), D8.1 (K), D9.1 (K), D10.1 (K), D11.1 (K), D12.1 (K), D13.1 (K), D14.1 (K), D15.1 (K), D16.1 (K), D17.1 (K), U1.4, U2.4, U3.2 (GND), U4.GND, U5.4
LF_SW: R8.2, SW1.2, U4.PK2
LM_SW: R9.2, SW2.2, U4.PK3
LR_SW: R10.2, SW3.2, U4.PN4
Lspeed: R5.2, U4.PD5
unnamed: D1.2 (A), R15.1
unnamed: D2.2 (A), R1.1
unnamed: D3.2 (A), R2.1
unnamed: D4.2 (A), R3.1
unnamed: D5.2 (A), R4.1
unnamed: D6.2 (A), R5.1
unnamed: D7.2 (A), R6.1
unnamed: D8.2 (A), R7.1
unnamed: D9.2 (A), R16.1
unnamed: D10.2 (A), R17.1
unnamed: D11.2 (A), R8.1
unnamed: D12.2 (A), R9.1
unnamed: D13.2 (A), R10.1
unnamed: D14.2 (A), R11.1
unnamed: D15.2 (A), R12.1
unnamed: D16.2 (A), R13.1
unnamed: D17.2 (A), R14.1
RF_SW: R11.2, SW4.2, U4.PN5
RM_SW: R12.2, SW5.2, U4.PP4
RR_SW: R13.2, SW6.2, U4.PQ0
RX_1: Conn5.3, R15.2, U1.2, U4.PK0
RX_2: Conn6.3, R16.2, U2.2, U4.PP0
RX_3: Conn7.3, R17.2, U4.PA4, U5.2
Rspeed: R6.2, U4.PD4
TX_1: Conn5.1, R2.2, U1.3, U4.PK1
TX_2: Conn6.1, R3.2, U2.3, U4.PP1
TX_3: Conn7.1, R4.2, U4.PA5, U5.3
Watchdog: R7.2, U4.PB5
Y1: Conn2.5, U1.5
Y2: Conn3.5, U2.5
Y3: Conn4.5, U5.5
Z1: Conn2.4, U1.6
Z2: Conn3.4, U2.6
Z3: Conn4.4, U5.6

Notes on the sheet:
Connectors
Tiva Headers
Power Filtering
Level Shifters
Motor 1,2
Motor 3,4
Motor 5,6
Serial 4
Serial 3
Serial 6
LED Indicators
Interface
Yellow
Green
Red
